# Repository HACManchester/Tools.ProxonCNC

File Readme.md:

# Tools.ProxonCNC

Project related information on the setup of the Proxon CNC within the space <br>
see the MkDocs directory for documentation

  * mkdocs url: http://HACManchester.github.io/Tools.ProxxonCNC

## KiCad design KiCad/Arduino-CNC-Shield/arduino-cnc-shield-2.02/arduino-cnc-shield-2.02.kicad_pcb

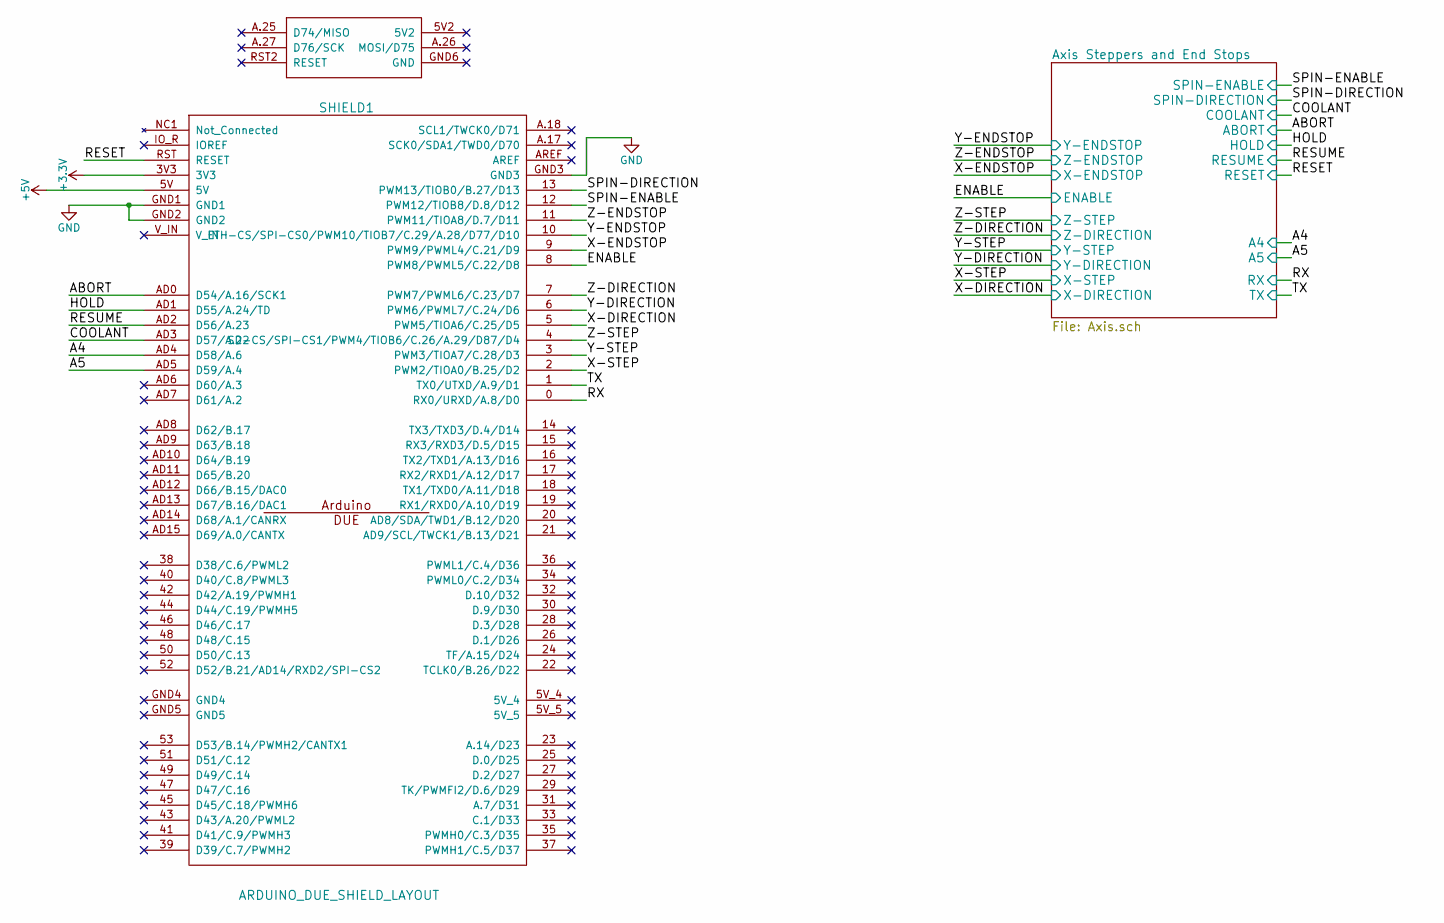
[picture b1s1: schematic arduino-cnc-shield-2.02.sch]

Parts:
SHIELD1: ARDUINO_DUE_SHIELD_LAYOUT; ARDUINO_SHIELD_2_SMALLPAD

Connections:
+3V3: SHIELD1.3V3
+5V: SHIELD1.5V; also elsewhere on the board
/Axis Steppers and End Stops/A4: SHIELD1.AD4 (D58/A.6); also elsewhere on the board
/Axis Steppers and End Stops/A5: SHIELD1.AD5 (D59/A.4); also elsewhere on the board
/Axis Steppers and End Stops/ABORT: SHIELD1.AD0 (D54/A.16/SCK1); also elsewhere on the board
/Axis Steppers and End Stops/COOLANT: SHIELD1.AD3 (D57/A.22); also elsewhere on the board
/Axis Steppers and End Stops/ENABLE: SHIELD1.8 (PWM8/PWML5/C.22/D8); also elsewhere on the board
/Axis Steppers and End Stops/HOLD: SHIELD1.AD1 (D55/A.24/TD); also elsewhere on the board
/Axis Steppers and End Stops/RESET: SHIELD1.RST (RESET); also elsewhere on the board
/Axis Steppers and End Stops/RESUME: SHIELD1.AD2 (D56/A.23); also elsewhere on the board
/Axis Steppers and End Stops/RX: SHIELD1.0 (RX0/URXD/A.8/D0); also elsewhere on the board
/Axis Steppers and End Stops/SPIN-DIRECTION: SHIELD1.13 (PWM13/TIOB0/B.27/D13); also elsewhere on the board
/Axis Steppers and End Stops/SPIN-ENABLE: SHIELD1.12 (PWM12/TIOB8/D.8/D12); also elsewhere on the board
/Axis Steppers and End Stops/TX: SHIELD1.1 (TX0/UTXD/A.9/D1); also elsewhere on the board
/Axis Steppers and End Stops/X-DIRECTION: SHIELD1.5 (PWM5/TIOA6/C.25/D5); also elsewhere on the board
/Axis Steppers and End Stops/X-ENDSTOP: SHIELD1.9 (PWM9/PWML4/C.21/D9); also elsewhere on the board
/Axis Steppers and End Stops/X-STEP: SHIELD1.2 (PWM2/TIOA0/B.25/D2); also elsewhere on the board
/Axis Steppers and End Stops/Y-DIRECTION: SHIELD1.6 (PWM6/PWML7/C.24/D6); also elsewhere on the board
/Axis Steppers and End Stops/Y-ENDSTOP: SHIELD1.10 (ETH-CS/SPI-CS0/PWM10/TIOB7/C.29/A.28/D7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); also elsewhere on the board
/Axis Steppers and End Stops/Y-STEP: SHIELD1.3 (PWM3/TIOA7/C.28/D3); also elsewhere on the board
/Axis Steppers and End Stops/Z-DIRECTION: SHIELD1.7 (PWM7/PWML6/C.23/D7); also elsewhere on the board
/Axis Steppers and End Stops/Z-ENDSTOP: SHIELD1.11 (PWM11/TIOA8/D.7/D11); also elsewhere on the board
/Axis Steppers and End Stops/Z-STEP: SHIELD1.4 (SD-CS/SPI-CS1/PWM4/TIOB6/C.26/A.29/D87/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); also elsewhere on the board
GND: SHIELD1.GND1, SHIELD1.GND2, SHIELD1.GND3; also elsewhere on the board

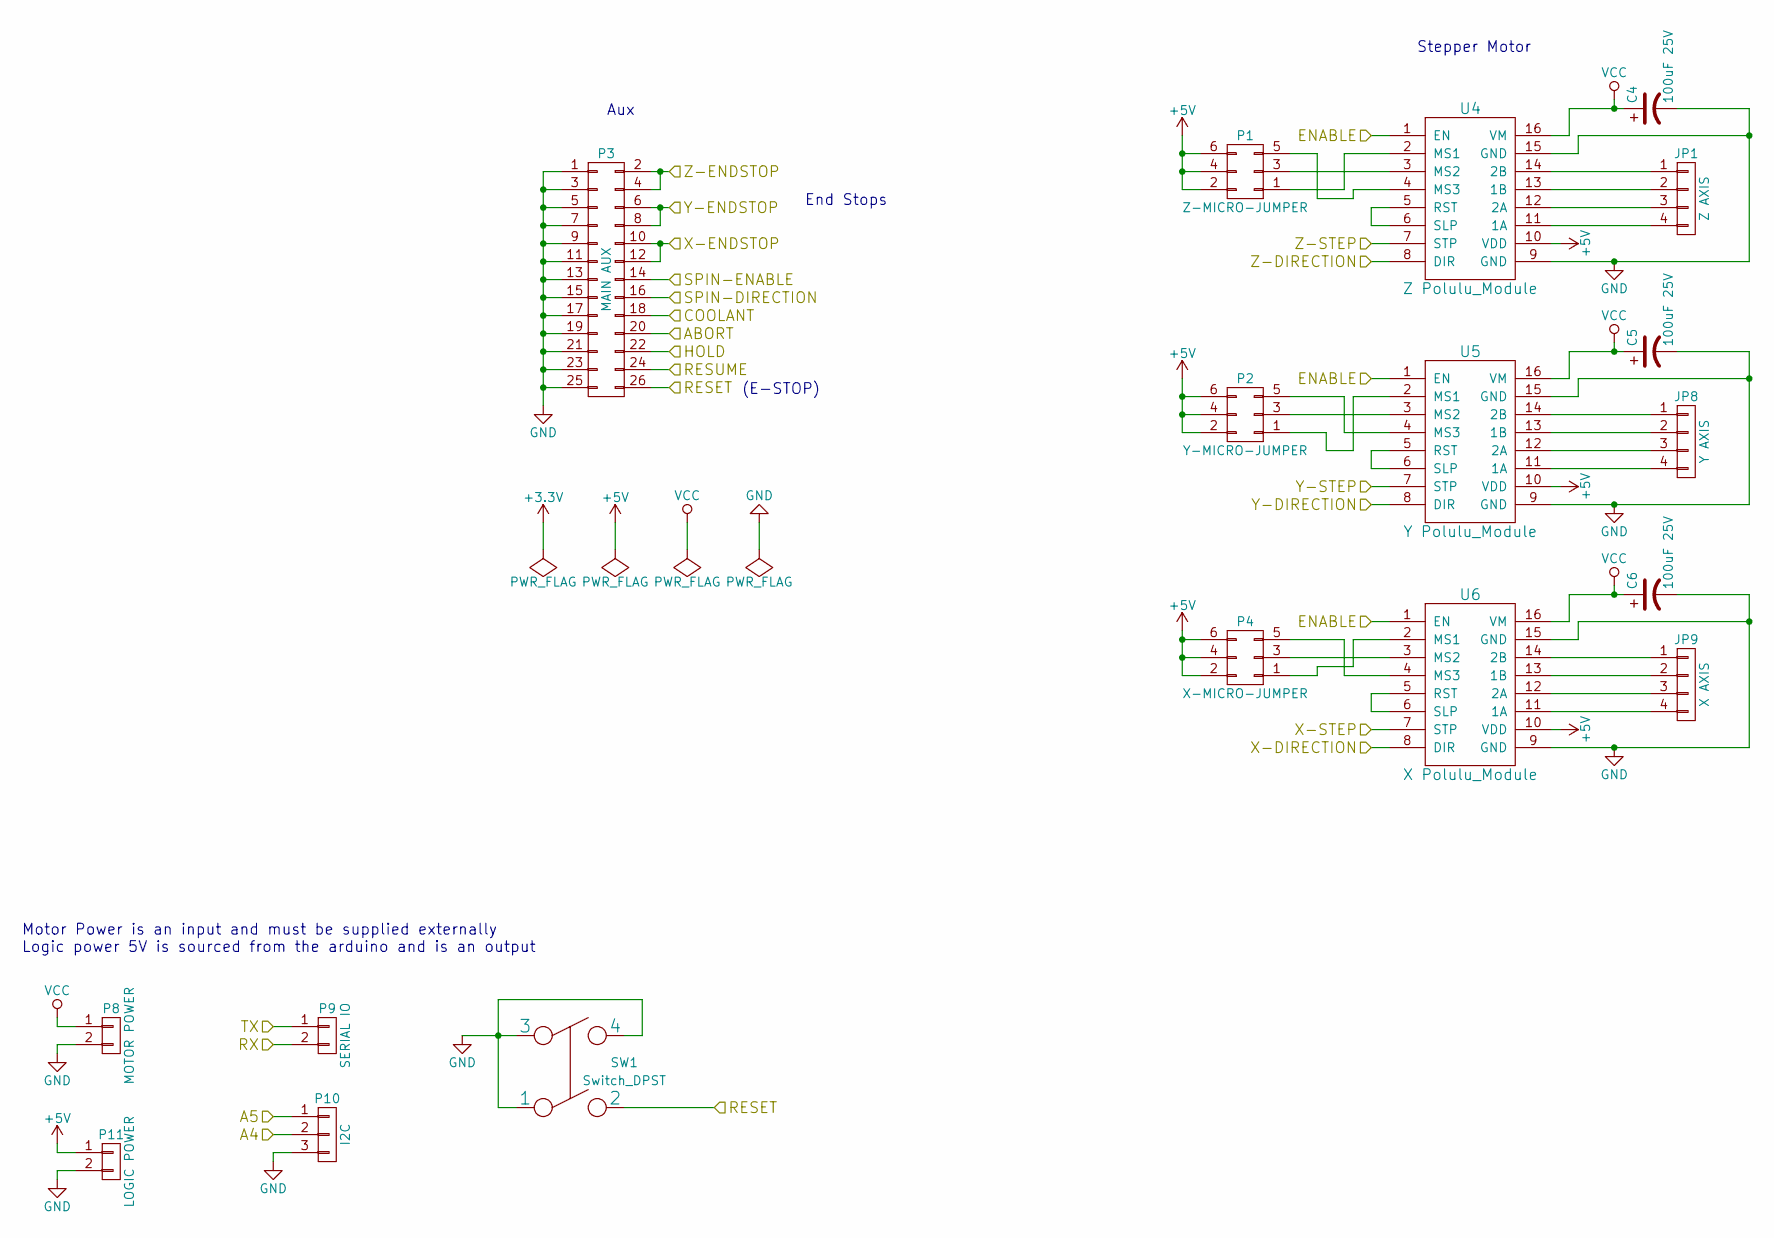
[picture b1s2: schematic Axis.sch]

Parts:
C4, C5, C6: 100uF 25V; Elko_vert_11.5x8mm_RM3.5
JP1: Z AXIS; Pin_Header_Straight_1x04
JP8: Y AXIS; Pin_Header_Straight_1x04
JP9: X AXIS; Pin_Header_Straight_1x04
P1: Z-MICRO-JUMPER; Pin_Header_Straight_2x03
P2: Y-MICRO-JUMPER; Pin_Header_Straight_2x03
P3: MAIN AUX; Pin_Header_Straight_2x13
P4: X-MICRO-JUMPER; Pin_Header_Straight_2x03
P8: MOTOR POWER; bornier2
P9: SERIAL IO; Pin_Header_Straight_1x02
P10: I2C; Pin_Header_Straight_1x03
P11: LOGIC POWER; Pin_Header_Straight_1x02
SW1: Switch_DPST
U4: Z Polulu_Module; Pololu_Module
U5: Y Polulu_Module; Pololu_Module
U6: X Polulu_Module; Pololu_Module

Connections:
+5V: P1.2, P1.4, P1.6, P2.2, P2.4, P2.6, P4.2, P4.4, P4.6, P11.1, U4.10 (VDD), U5.10 (VDD), U6.10 (VDD); also elsewhere on the board
/Axis Steppers and End Stops/A4: P10.2; also elsewhere on the board
/Axis Steppers and End Stops/A5: P10.1; also elsewhere on the board
/Axis Steppers and End Stops/ABORT: P3.20; also elsewhere on the board
/Axis Steppers and End Stops/COOLANT: P3.18; also elsewhere on the board
/Axis Steppers and End Stops/ENABLE: U4.1 (EN), U5.1 (EN), U6.1 (EN); also elsewhere on the board
/Axis Steppers and End Stops/HOLD: P3.22; also elsewhere on the board
/Axis Steppers and End Stops/RESET: P3.26, SW1.2; also elsewhere on the board
/Axis Steppers and End Stops/RESUME: P3.24; also elsewhere on the board
/Axis Steppers and End Stops/RX: P9.2; also elsewhere on the board
/Axis Steppers and End Stops/SPIN-DIRECTION: P3.16; also elsewhere on the board
/Axis Steppers and End Stops/SPIN-ENABLE: P3.14; also elsewhere on the board
/Axis Steppers and End Stops/TX: P9.1; also elsewhere on the board
/Axis Steppers and End Stops/X-DIRECTION: U6.8 (DIR); also elsewhere on the board
/Axis Steppers and End Stops/X-ENDSTOP: P3.10, P3.12; also elsewhere on the board
/Axis Steppers and End Stops/X-STEP: U6.7 (STP); also elsewhere on the board
/Axis Steppers and End Stops/Y-DIRECTION: U5.8 (DIR); also elsewhere on the board
/Axis Steppers and End Stops/Y-ENDSTOP: P3.6, P3.8; also elsewhere on the board
/Axis Steppers and End Stops/Y-STEP: U5.7 (STP); also elsewhere on the board
/Axis Steppers and End Stops/Z-DIRECTION: U4.8 (DIR); also elsewhere on the board
/Axis Steppers and End Stops/Z-ENDSTOP: P3.2, P3.4; also elsewhere on the board
/Axis Steppers and End Stops/Z-STEP: U4.7 (STP); also elsewhere on the board
GND: C4.2, C5.2, C6.2, P3.1, P3.3, P3.5, P3.7, P3.9, P3.11, P3.13, P3.15, P3.17, P3.19, P3.21, P3.23, P3.25, P8.2, P10.3, P11.2, SW1.1, SW1.3, SW1.4, U4.9 (GND), U4.15 (GND), U5.9 (GND), U5.15 (GND), U6.9 (GND), U6.15 (GND); also elsewhere on the board
unnamed: JP1.1, U4.14 (2B)
unnamed: JP1.2, U4.13 (1B)
unnamed: JP1.3, U4.12 (2A)
unnamed: JP1.4, U4.11 (1A)
unnamed: JP8.1, U5.14 (2B)
unnamed: JP8.2, U5.13 (1B)
unnamed: JP8.3, U5.12 (2A)
unnamed: JP8.4, U5.11 (1A)
unnamed: JP9.1, U6.14 (2B)
unnamed: JP9.2, U6.13 (1B)
unnamed: JP9.3, U6.12 (2A)
unnamed: JP9.4, U6.11 (1A)
unnamed: P1.1, U4.2 (MS1)
unnamed: P1.3, U4.3 (MS2)
unnamed: P1.5, U4.4 (MS3)
unnamed: P2.1, U5.2 (MS1)
unnamed: P2.3, U5.3 (MS2)
unnamed: P2.5, U5.4 (MS3)
unnamed: P4.1, U6.2 (MS1)
unnamed: P4.3, U6.3 (MS2)
unnamed: P4.5, U6.4 (MS3)
unnamed: U4.5 (RST), U4.6 (SLP)
unnamed: U5.5 (RST), U5.6 (SLP)
unnamed: U6.5 (RST), U6.6 (SLP)
VCC: C4.1, C5.1, C6.1, P8.1, U4.16 (VM), U5.16 (VM), U6.16 (VM)

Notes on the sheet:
Aux
Stepper Motor
End Stops
Motor Power is an input and must be supplied externally Logic power 5V is sourced from the arduino and is an output
(E-STOP)

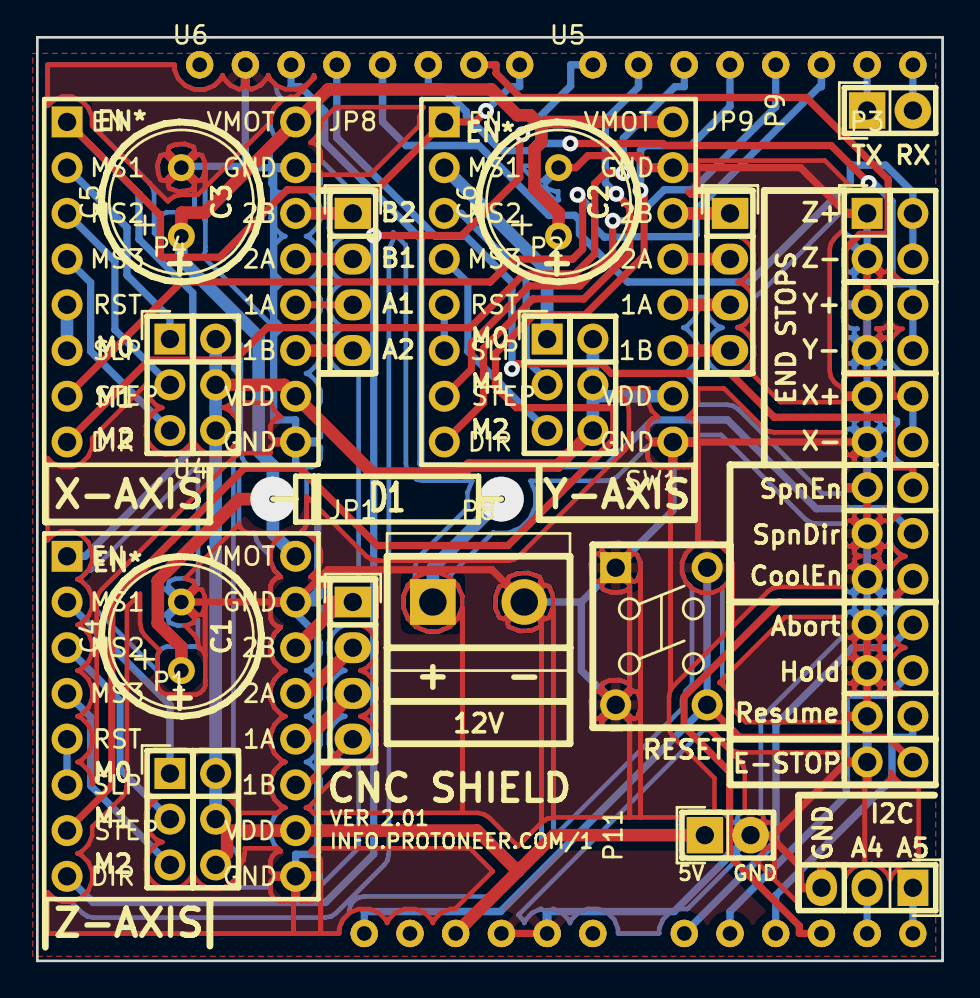
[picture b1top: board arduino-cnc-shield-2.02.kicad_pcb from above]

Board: 2 copper layers, 50.3 x 51.3 mm, 19 parts (0 on the bottom side), 48 nets.

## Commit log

2016-03-09 Add of git ignore
2016-03-10 more docs
2016-03-10 Deployed c191b72 with MkDocs version: 0.15.3
2016-03-10 minor doc changes
2016-03-10 Deployed e196a9f with MkDocs version: 0.15.3
2016-03-10 Old circuit diagram
2016-03-18 Initial import of flow diagrams
2016-03-18 Deployed 43c0d89 with MkDocs version: 0.15.3
